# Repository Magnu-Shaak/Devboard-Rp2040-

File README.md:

# Devboard-Rp2040-

This is a devboard following the Kai Pereira tutorial. However, there are 2 major differences:
- 1: Mine breaks out all pins while following the Pi-Pico layout*(mostly). He followed the Pi-Pico layout too*, but I also added 2 1x2 connectors which I used to break out the final GPIO pin, and provide easy access to 3v3 and VBUS from the bottom of the board. This greatly benefits the left side, as it now has an ADC pin and power access from the bottom, instead of needing to run traces to the other side of the board. And despite moving the 3 pin connector (used for debugging) up, some Pi Pico boards have it in the center anyways, so this doesn't make in incompatible as a drop in replacement either(unless its battery operated).
- 2: I also have opted to use the higher power rated LDO for my 3v3 line, whereas he swapped to a lower power rated one for space. Just better overall.

I made these changes for convenience. Having a better LDO is generally just better and the ADC and power pin breakouts are really convenient and help reduce congestion below the chip.

*Replaced some unused i/o pins (VSYS, 3v3_EN, ADC_REF) to breakout some 3 more GPIO pins

## For Reproducing
If you are recreating this yourself, look at the Readme in production for more information.

BOM:
| Item                  |  Quantity | Listed Price | Total Cost [for me]  (shipping, sales tax) | Link                                  | Source  | Notes              |
|-----------------------|-----------|--------------|--------------------------------------------|---------------------------------------|---------|--------------------|
| PCB                   | 5         | 2            | 2                                          | https://cart.jlcpcb.com/shopcart/cart | JLCPCB  | $2 deal            |
| PCBA                  | 2         | 33.13        | 33.13                                      | https://cart.jlcpcb.com/shopcart/cart | JLCPCB  |                    |
| Custom Duties & Taxes |           | 12.24        | 12.24                                      | https://cart.jlcpcb.com/shopcart/cart | JLCPCB  | US Customs         |
| JLC Shipping (DDP)    |           | 29.98        | 29.98                                      | https://cart.jlcpcb.com/shopcart/cart | JLCPCB  | UPS Express (DDP)  |
| SMT PCBA Coupon       |           | -10          | -10                                        | https://cart.jlcpcb.com/shopcart/cart | JLC PCB | New Account Coupon |
|                       |           |              |                                            | https://cart.jlcpcb.com/shopcart/cart |         |                    |
| Total                 | 7         | 67.35        | 67.35                                      | https://excel.cloud.microsoft/en-us |         |                    |

The extra connectors I added:

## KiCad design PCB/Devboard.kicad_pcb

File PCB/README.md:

Creating PCB folder

 - Zipped gerbers are under Production

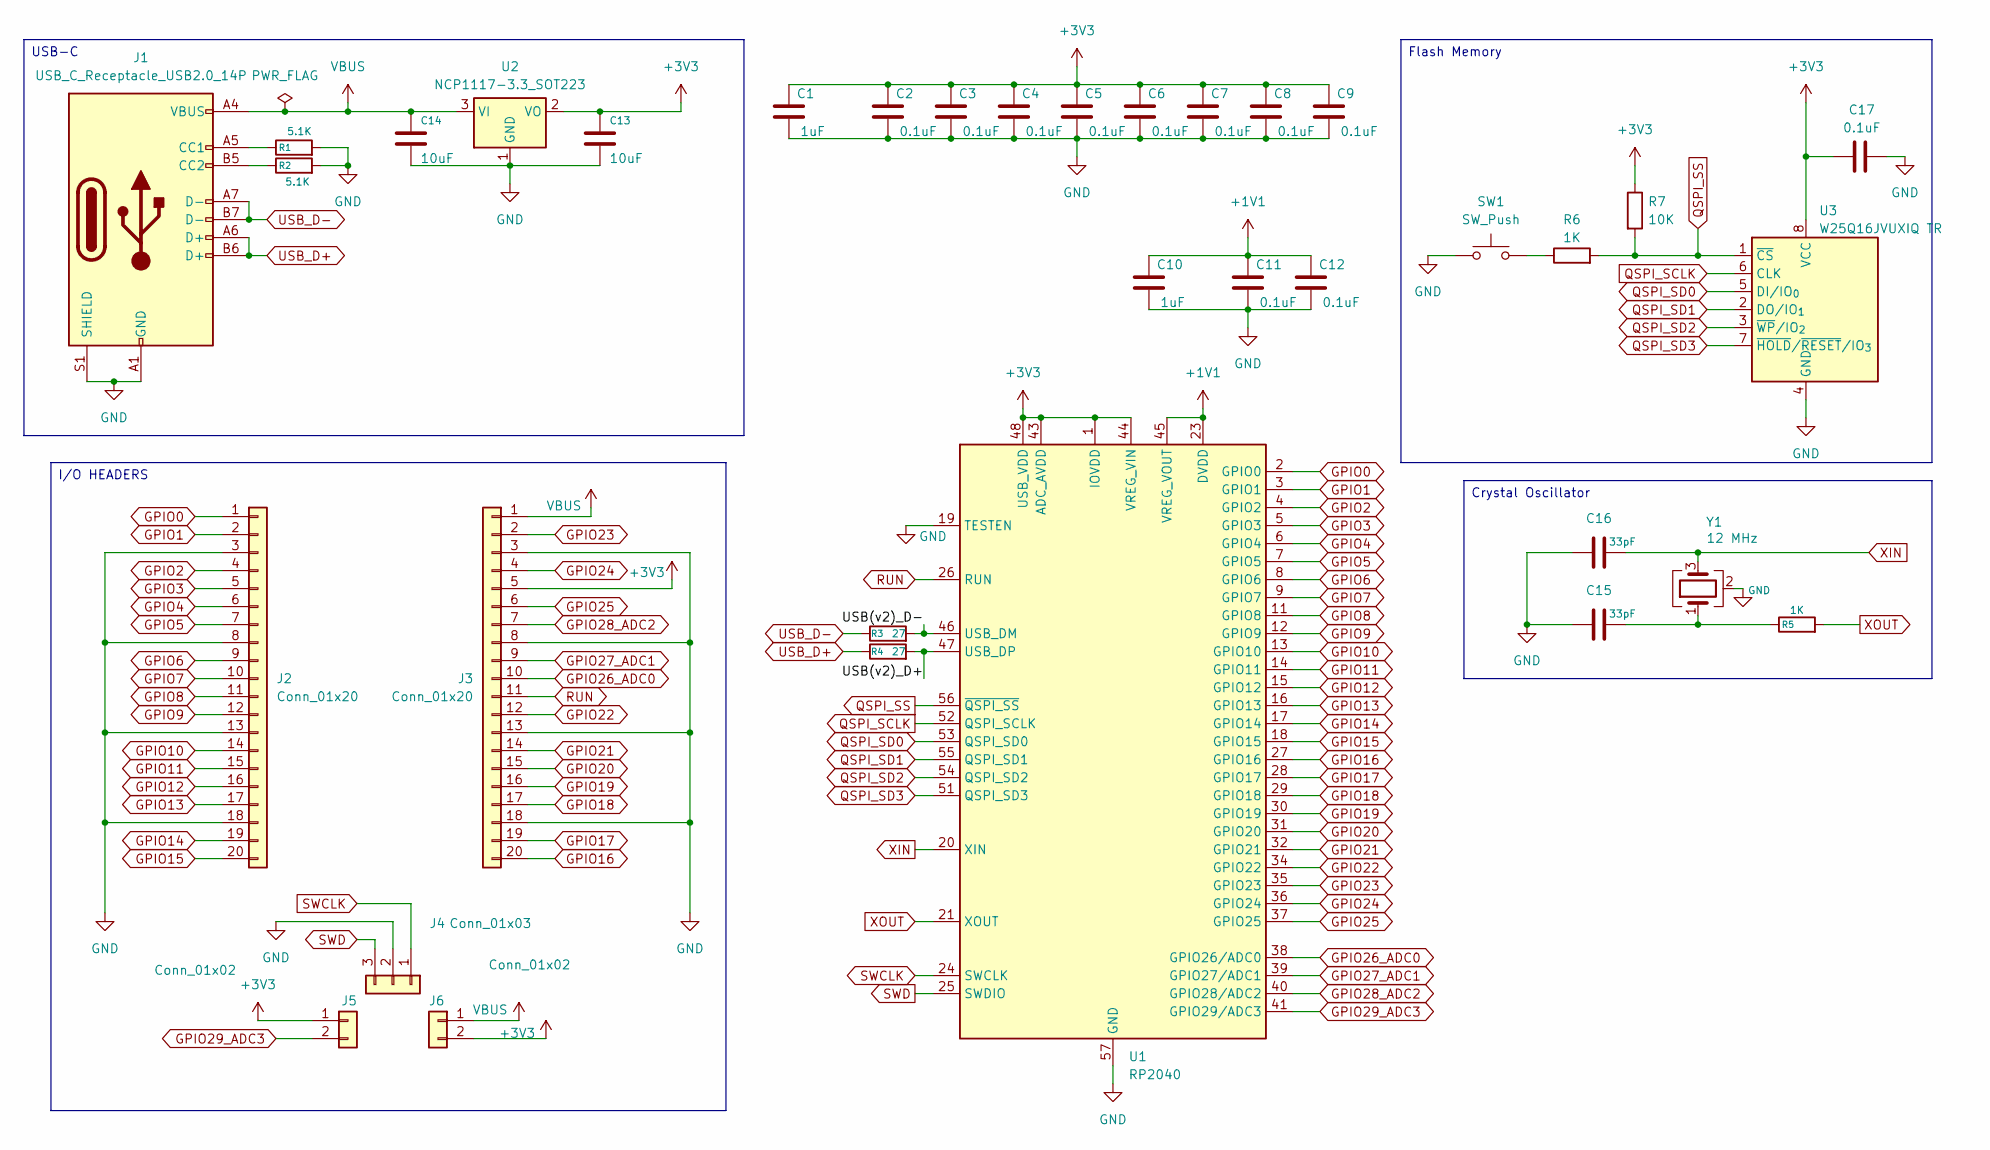
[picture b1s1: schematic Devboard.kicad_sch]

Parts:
C1, C10: 1uF; C_0402_1005Metric
C2, C3, C4, C5, C6, C7, C8, C9, C11, C12, C17: 0.1uF; C_0402_1005Metric
C13, C14: 10uF; C_0603_1608Metric
C15, C16: 33pF; C_0402_1005Metric
J1: USB_C_Receptacle_USB2.0_14P; USB_C_Receptacle_HRO_TYPE-C-31-M-12
J2, J3: Conn_01x20; PinHeader_1x20_P2.54mm_Vertical
J4: Conn_01x03; PinHeader_1x03_P2.54mm_Vertical
J5, J6: Conn_01x02; PinHeader_1x02_P2.54mm_Vertical
R1, R2: 5.1K; R_0402_1005Metric
R3, R4: 27; R_0402_1005Metric
R5, R6: 1K; R_0402_1005Metric
R7: 10K; R_0402_1005Metric
SW1: SW_Push; SW_Push_SPST_NO_Alps_SKRK
U1: RP2040; QFN-56-1EP_7x7mm_P0.4mm_EP3.2x3.2mm
U2: NCP1117-3.3_SOT223; SOT-223-3_TabPin2
U3: W25Q16JVUXIQ TR; Winbond_USON-8-1EP_3x2mm_P0.5mm_EP0.2x1.6mm
Y1: 12 MHz; Crystal_SMD_3225-4Pin_3.2x2.5mm

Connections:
+1V1: C10.1, C11.1, C12.1, U1.23 (DVDD), U1.45 (VREG_VOUT), U1.50 (DVDD)
+3V3: C1.1, C2.1, C3.1, C4.1, C5.1, C6.1, C7.1, C8.1, C9.1, C13.1, C17.1, J3.5, J5.1, J6.2, R7.1, U1.1 (IOVDD), U1.10 (IOVDD), U1.22 (IOVDD), U1.33 (IOVDD), U1.42 (IOVDD), U1.43 (ADC_AVDD), U1.44 (VREG_VIN), U1.48 (USB_VDD), U1.49 (IOVDD), U2.2 (VO), U3.8 (VCC)
/USB(v2)_D+: R4.2, U1.47 (USB_DP)
/USB(v2)_D-: R3.2, U1.46 (USB_DM)
GND: C1.2, C2.2, C3.2, C4.2, C5.2, C6.2, C7.2, C8.2, C9.2, C10.2, C11.2, C12.2, C13.2, C14.2, C15.1, C16.1, C17.2, J1.A1 (GND), J1.A12 (GND), J1.B1 (GND), J1.B12 (GND), J1.S1 (SHIELD), J2.3, J2.8, J2.13, J2.18, J3.3, J3.8, J3.13, J3.18, J4.2, R1.2, R2.2, SW1.1, U1.19 (TESTEN), U1.57 (GND), U2.1 (GND), U3.4 (GND), Y1.2 (G), Y1.4 (G)
GPIO0: J2.1, U1.2 (GPIO0)
GPIO1: J2.2, U1.3 (GPIO1)
GPIO2: J2.4, U1.4 (GPIO2)
GPIO3: J2.5, U1.5 (GPIO3)
GPIO4: J2.6, U1.6 (GPIO4)
GPIO5: J2.7, U1.7 (GPIO5)
GPIO6: J2.9, U1.8 (GPIO6)
GPIO7: J2.10, U1.9 (GPIO7)
GPIO8: J2.11, U1.11 (GPIO8)
GPIO9: J2.12, U1.12 (GPIO9)
GPIO10: J2.14, U1.13 (GPIO10)
GPIO11: J2.15, U1.14 (GPIO11)
GPIO12: J2.16, U1.15 (GPIO12)
GPIO13: J2.17, U1.16 (GPIO13)
GPIO14: J2.19, U1.17 (GPIO14)
GPIO15: J2.20, U1.18 (GPIO15)
GPIO16: J3.20, U1.27 (GPIO16)
GPIO17: J3.19, U1.28 (GPIO17)
GPIO18: J3.17, U1.29 (GPIO18)
GPIO19: J3.16, U1.30 (GPIO19)
GPIO20: J3.15, U1.31 (GPIO20)
GPIO21: J3.14, U1.32 (GPIO21)
GPIO22: J3.12, U1.34 (GPIO22)
GPIO23: J3.2, U1.35 (GPIO23)
GPIO24: J3.4, U1.36 (GPIO24)
GPIO25: J3.6, U1.37 (GPIO25)
GPIO26_ADC0: J3.10, U1.38 (GPIO26/ADC0)
GPIO27_ADC1: J3.9, U1.39 (GPIO27/ADC1)
GPIO28_ADC2: J3.7, U1.40 (GPIO28/ADC2)
GPIO29_ADC3: J5.2, U1.41 (GPIO29/ADC3)
unnamed: C15.2, R5.1, Y1.1
unnamed: J1.A5 (CC1), R1.1
unnamed: J1.B5 (CC2), R2.1
unnamed: R6.1, SW1.2
QSPI_SCLK: U1.52 (QSPI_SCLK), U3.6 (CLK)
QSPI_SD0: U1.53 (QSPI_SD0), U3.5 (DI/IO_{0})
QSPI_SD1: U1.55 (QSPI_SD1), U3.2 (DO/IO_{1})
QSPI_SD2: U1.54 (QSPI_SD2), U3.3 (~WP/IO_{2})
QSPI_SD3: U1.51 (QSPI_SD3), U3.7 (~HOLD/~RESET/IO_{3})
QSPI_SS: R6.2, R7.2, U1.56 (~QSPI_SS), U3.1 (~CS)
RUN: J3.11, U1.26 (RUN)
SWCLK: J4.1, U1.24 (SWCLK)
SWD: J4.3, U1.25 (SWDIO)
USB_D+: J1.A6 (D+), J1.B6 (D+), R4.1
USB_D-: J1.A7 (D-), J1.B7 (D-), R3.1
VBUS: C14.1, J1.A4 (VBUS), J1.A9 (VBUS), J1.B4 (VBUS), J1.B9 (VBUS), J3.1, J6.1, U2.3 (VI)
XIN: C16.2, U1.20 (XIN), Y1.3
XOUT: R5.2, U1.21 (XOUT)

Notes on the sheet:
Flash Memory
Crystal Oscillator
I/O HEADERS
USB-C

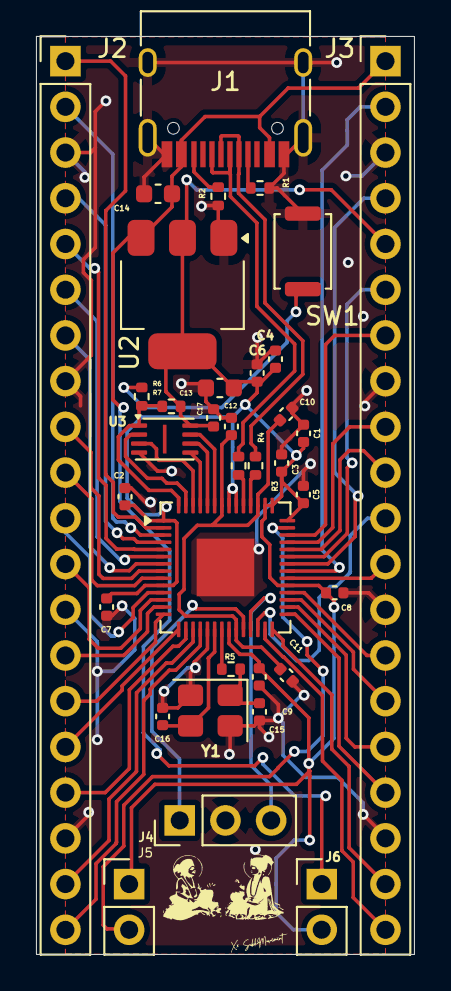
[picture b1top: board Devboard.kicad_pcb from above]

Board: 2 copper layers, 21.0 x 51.0 mm, 35 parts (0 on the bottom side), 53 nets.

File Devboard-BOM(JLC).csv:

Designator,Footprint,Quantity,Comment,LCSC Part #
"C1,C10",Capacitor_SMD:C_0402_1005Metric,2,1uF,
"C2,C3,C4,C5,C6,C7,C8,C9,C11,C12,C17",Capacitor_SMD:C_0402_1005Metric,11,0.1uF,
"C13,C14",Capacitor_SMD:C_0603_1608Metric,2,10uF,
"C15,C16",Capacitor_SMD:C_0402_1005Metric,2,33pF,
J1,Connector_USB:USB_C_Receptacle_HRO_TYPE-C-31-M-12,1,USB_C_Receptacle_USB2.0_14P,
"J2,J3",Connector_PinHeader_2.54mm:PinHeader_1x20_P2.54mm_Vertical,2,Conn_01x20,
J4,Connector_PinHeader_2.54mm:PinHeader_1x03_P2.54mm_Vertical,1,Conn_01x03,
"J5,J6",Connector_PinHeader_2.54mm:PinHeader_1x02_P2.54mm_Vertical,2,Conn_01x02,
"R1,R2",Resistor_SMD:R_0402_1005Metric,2,5.1K,
"R3,R4",Resistor_SMD:R_0402_1005Metric,2,27,
"R5,R6",Resistor_SMD:R_0402_1005Metric,2,1K,
R7,Resistor_SMD:R_0402_1005Metric,1,10K,
SW1,Button_Switch_SMD:SW_Push_SPST_NO_Alps_SKRK,1,SW_Push,
U1,Package_DFN_QFN:QFN-56-1EP_7x7mm_P0.4mm_EP3.2x3.2mm,1,RP2040,
U2,Package_TO_SOT_SMD:SOT-223-3_TabPin2,1,NCP1117-3.3_SOT223,
U3,Package_SON:Winbond_USON-8-1EP_3x2mm_P0.5mm_EP0.2x1.6mm,1,W25Q16JVUXIQ TR,
Y1,Crystal:Crystal_SMD_3225-4Pin_3.2x2.5mm,1,12 MHz,
